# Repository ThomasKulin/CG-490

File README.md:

# CG-490
shooting stuff with electricity. yes

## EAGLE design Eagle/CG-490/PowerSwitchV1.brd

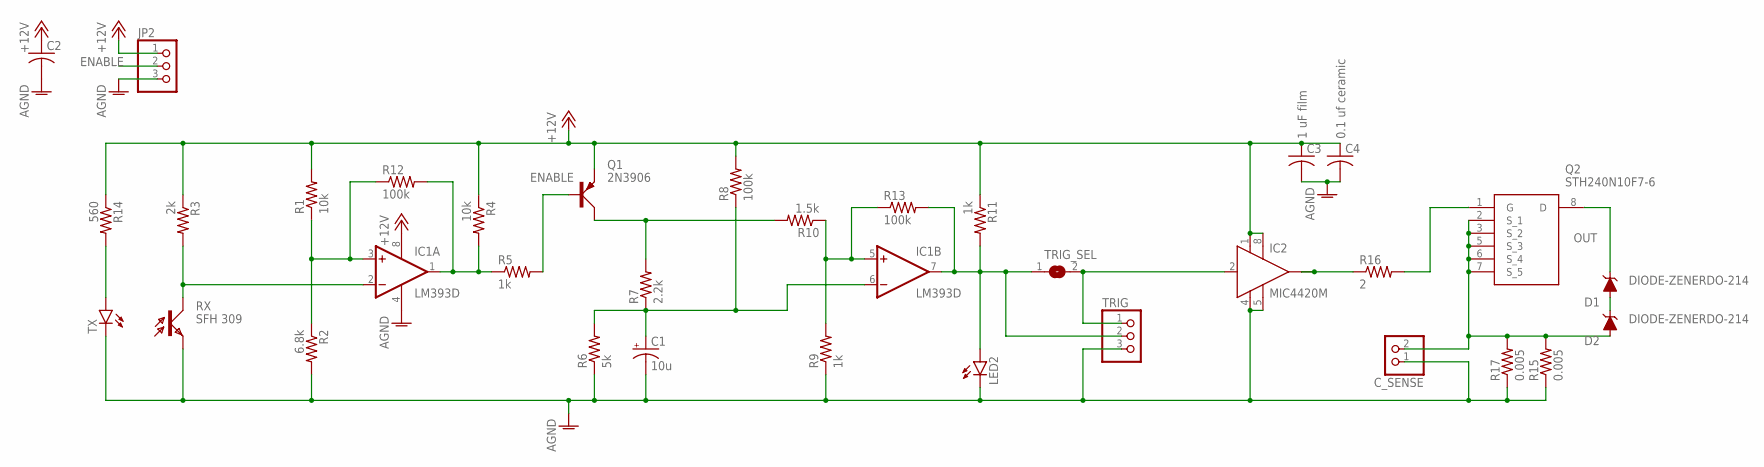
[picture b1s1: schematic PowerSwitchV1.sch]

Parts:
C1: 10u; TT2D6
C2: C-US050-050X075; C050-050X075
C3: 1 uF film; C050-045X075
C4: 0.1 uf ceramic; C025-030X050
C_SENSE: PINHD-1X2; 1X02
D1, D2: DIODE-ZENERDO-214; SMA-DIODE
IC1: LM393D; SO08
IC2: MIC4420M; SO-08
JP2: PINHD-1X3; 1X03
LED2: LEDCHIPLED_0603; CHIPLED_0603
Q1: 2N3906; TO92D
Q2: STH240N10F7-6; H2PAK-6_1
R1, R4: 10k; R0603
R2: 6.8k; R0603
R3: 2k; R0603
R5, R9, R11: 1k; R0603
R6: 5k; R0603
R7: 2.2k; R0603
R8, R12, R13: 100k; R0603
R10: 1.5k; R0603
R14: 560; R0603
R15, R17: 0.005; R1206
R16: 2; M0805
RX: SFH 309; BPX81
TRIG: PINHD-1X3; 1X03
TRIG_SEL: SJ
TX: LED3MM

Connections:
+12V: C2.1, C3.1, C4.1, IC1.8 (V+), IC2.1 (VS), IC2.8 (VS1), JP2.1, Q1.E, R1.2, R3.1, R4.1, R8.2, R11.1, R14.1
AGND: C1.-, C2.2, C3.2, C4.2, C_SENSE.1, IC1.4 (V-), IC2.4 (GND), IC2.5 (GND1), JP2.3, LED2.C, R2.2, R6.1, R9.1, R15.1, R17.1, RX.E, TRIG.3, TX.K (C)
ENABLE: JP2.2, Q1.B, R5.2
unnamed: IC1.2 (-IN), R3.2, RX.C
unnamed: IC2.2 (IN), TRIG.1, TRIG_SEL.2
unnamed: IC1.3 (+IN), R1.1, R2.1, R12.1
unnamed: IC2.6 (OUT), IC2.7 (OUT), R16.1
unnamed: IC1.1 (OUT), R4.2, R5.1, R12.2
unnamed: Q1.C, R7.2, R10.2
unnamed: C1.+, IC1.6 (-IN), R6.2, R7.1, R8.1
unnamed: R14.2, TX.A
unnamed: D1.A, D2.C
unnamed: IC1.5 (+IN), R9.2, R10.1, R13.1
unnamed: IC1.7 (OUT), LED2.A, R11.2, R13.2, TRIG.2, TRIG_SEL.1
unnamed: C_SENSE.2, D2.A, Q2.2 (S_1), Q2.3 (S_2), Q2.5 (S_3), Q2.6 (S_4), Q2.7 (S_5), R15.2, R17.2
unnamed: Q2.1 (G), R16.2
OUT: D1.C, Q2.8 (D)

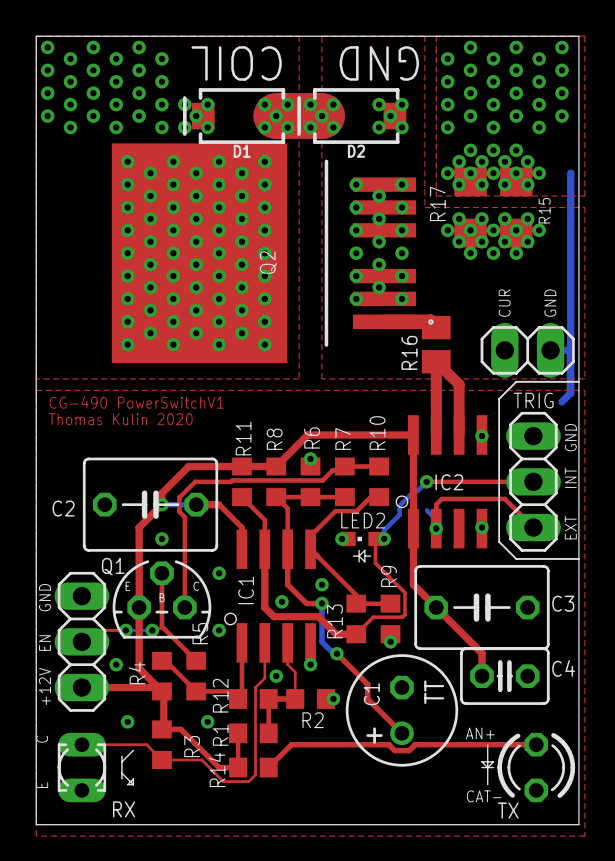
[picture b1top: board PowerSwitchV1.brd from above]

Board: 2 copper layers, 30.1 x 43.8 mm, 34 parts (1 on the bottom side), 17 nets.

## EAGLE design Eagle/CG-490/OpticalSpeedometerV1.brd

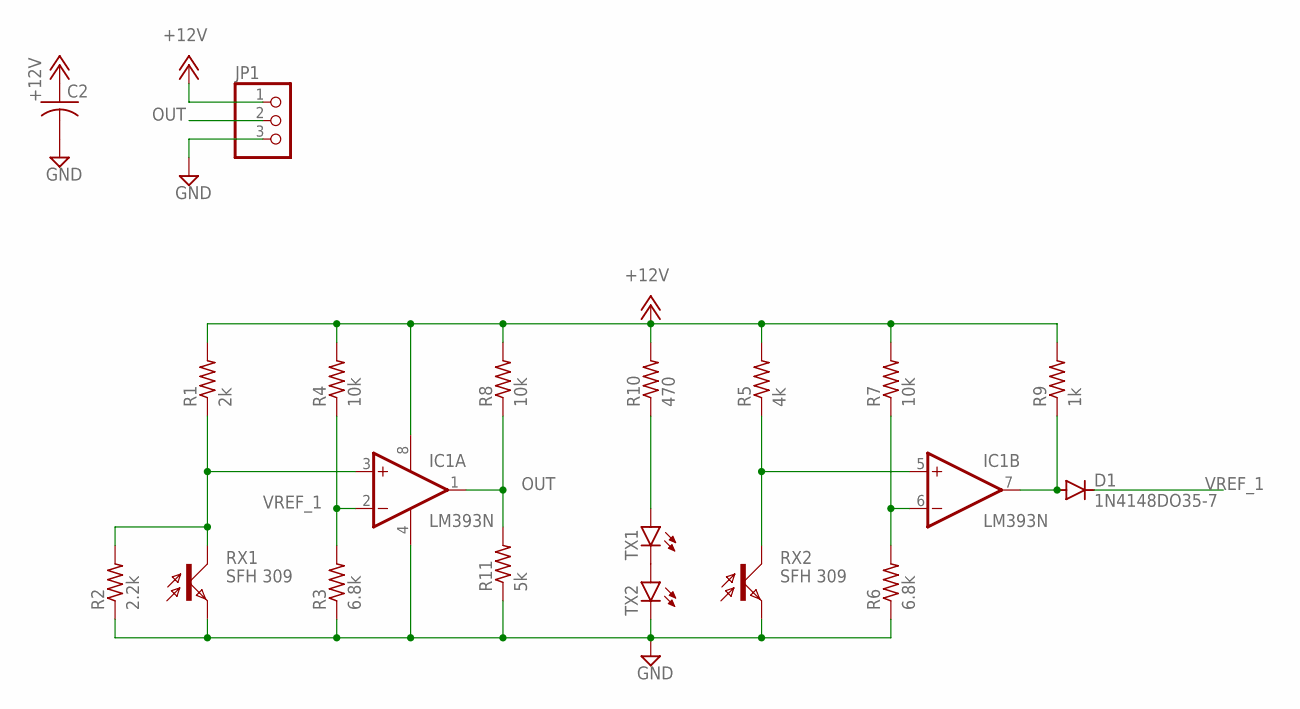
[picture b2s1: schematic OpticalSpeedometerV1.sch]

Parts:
C2: C-US050-050X075; C050-050X075
D1: 1N4148DO35-7; DO35-7
IC1: LM393N; DIL08
JP1: PINHD-1X3; 1X03
R1: 2k; 0204/5
R2: 2.2k; 0204/5
R3, R6: 6.8k; 0204/5
R4, R7, R8: 10k; 0204/5
R5: 4k; 0204/5
R9: 1k; 0204/5
R10: 470; 0204/5
R11: 5k; 0204/5
RX1, RX2: SFH 309; BPX81
TX1, TX2: LED3MM

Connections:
+12V: C2.1, IC1.8 (V+), JP1.1, R1.2, R4.2, R5.2, R7.2, R8.2, R9.2, R10.2
GND: C2.2, IC1.4 (V-), JP1.3, R2.1, R3.1, R6.1, R11.1, RX1.E, RX2.E, TX2.K (C)
unnamed: TX1.K (C), TX2.A
unnamed: IC1.3 (+IN), R1.1, R2.2, RX1.C
unnamed: R10.1, TX1.A
unnamed: IC1.5 (+IN), R5.1, RX2.C
unnamed: IC1.6 (-IN), R6.2, R7.1
unnamed: D1.A, IC1.7 (OUT), R9.1
OUT: IC1.1 (OUT), JP1.2, R8.1, R11.2
VREF_1: D1.C, IC1.2 (-IN), R3.2, R4.1

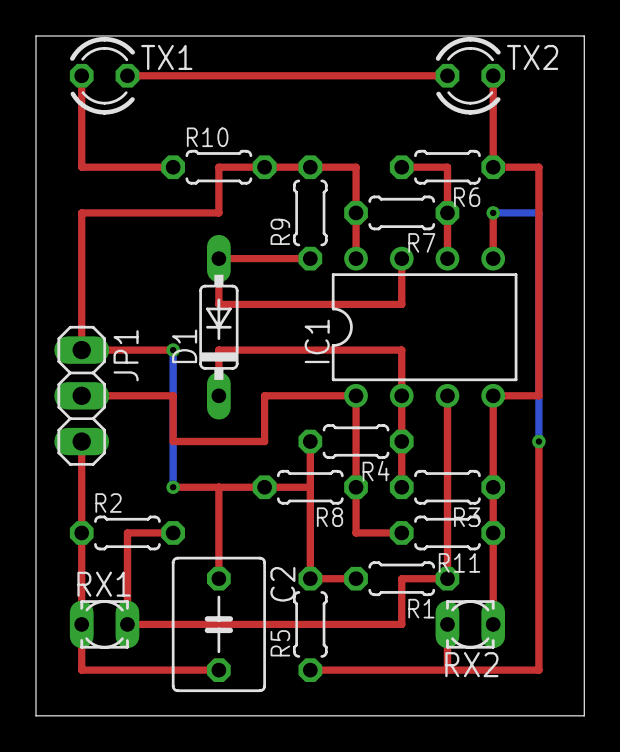
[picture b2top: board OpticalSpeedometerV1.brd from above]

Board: 2 copper layers, 30.5 x 37.8 mm, 19 parts (0 on the bottom side), 10 nets.

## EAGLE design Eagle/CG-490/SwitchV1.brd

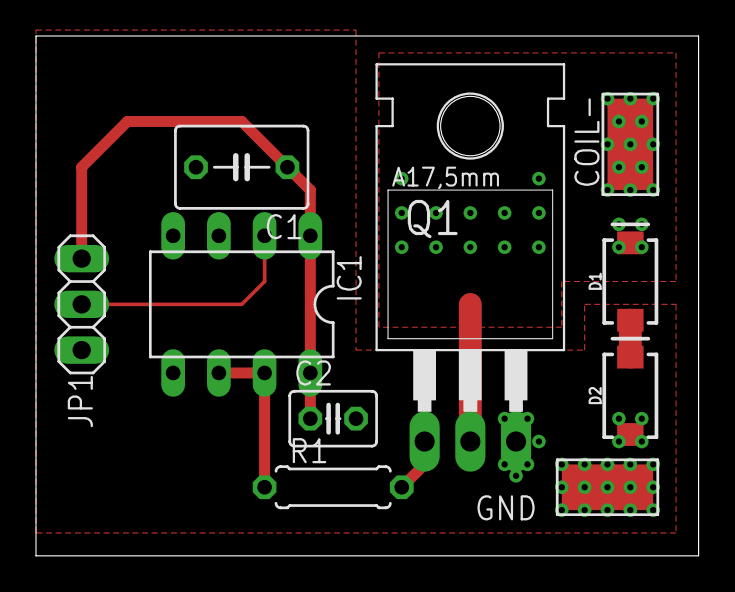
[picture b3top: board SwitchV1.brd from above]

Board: 2 copper layers, 36.8 x 28.9 mm, 10 parts (0 on the bottom side), 7 nets.

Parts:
C1: 1 uF film; C050-045X075
C2: 0.1 uf ceramic; C025-030X050
COIL-: WIREPADSMD5-2,5; 5-2,5
D1, D2: DIODE-ZENERDO-214; SMA-DIODE
GND: WIREPADSMD5-2,5; 5-2,5
IC1: MIC4420N; DIL08
JP1: 1X03
Q1: IRF540; TO220
R1: 1; 0207/7

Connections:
+18V: C1.1, C2.1, IC1.1, IC1.8, JP1.1
GND: C1.2, C2.2, D2.A, GND.1, IC1.4, IC1.5, JP1.3, Q1.3
unnamed: IC1.6, IC1.7, R1.1
unnamed: Q1.1, R1.2
unnamed: D1.A, D2.C
unnamed: IC1.2, JP1.2
OUT: COIL-.1, D1.C, Q1.2

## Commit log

2019-10-16 preliminary SPICE and FEMM simulations along with python automated tests in progress
2019-10-17 updated time sweep test, added thermal model to simulations
2019-10-18 atarted implementing a femm sim sweeping length, radius of projectile while maintaining a constant coil inductance
2019-10-21 dimensional sweep test functional. need to add better data capture
2019-10-22 ran some simulations to determine optimal projectile diameter for a 40uH coil, 12mm seems like the sweet spot. need to sweep length at that radius
2019-10-23 Added Inductance sweep test. Concludes that higher inductance is better but only a little. Width still has huge effects on the projectile..
2019-10-23 Started writing the simulation writeup report
2019-10-24 updated write-up
2019-10-25 updated doc, added new links
2019-10-29 started final cicuit model
2019-10-29 updated report
2019-10-29 added prototype switch schematic
2019-10-30 added prototype layout and added to report
2019-10-30 started FEMM sim write-up, finished switch sim write-up
2019-10-31 added fixed resistance mode for FEMM sims
2019-11-01 fixed fixedresistance mode. captured length dimension sweep with constant resistance. wrote some stuff. hi thomas
2019-11-01 added some stuff but i dont remember what
2019-11-05 added 2d plots for dimension sweep
2019-11-12 added LT Spice simulation integration into python scripts to facilitate more accurate simulation at higher inductances
2019-11-13 started updated timesweep test
2019-11-14 completed integration of current waveform in time based simulation. Next step is to make it multi stage
2019-11-14 got some nice data
2019-11-14 completed simultion of first stage, started simulation of subsequent stages, updated report
2019-11-20 not much
2019-11-21 designed optical trigger with pulse limiting mechanism, ran LT simulations
2019-11-22 updated optical switch schematic. needs better biasing on comparator 2 to ensure noise proof performance. also editing report.
2019-11-24 Added time based external iron test and object
2019-11-25 worked on report
2019-11-25 did some external iron testing for stage 1. Not feasible
2019-11-26 first commie
2020-01-31 ran simulation of real world stage 1 design, created optical assembly CAD file
2020-02-10 updated report with opt triggering circuit performance and finalized magnetic sim for first stage
2020-02-13 fuck, i just shorted the LIPO through a bunch of shit....
2020-03-05 layout for optical trigger and complete circuit underway
2020-03-05 updated document with test results
2020-03-05 updated board layouts
2020-03-06 updated components in 3d model of PCB
2020-03-10 finalized schematic/pcb, updated report
2020-03-12 updated board layout
2020-03-19 idk, just syncing
2020-03-22 made optical speed sensor sim, circuit and perfboard layout
2020-09-17 updated report and made minor changes with the boys
2021-10-10 sync

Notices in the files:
parts and their libraries:
sparkfun-discretesemi: Licensing: Creative Commons ShareAlike 4.0 International - https://creativecommons.org/licenses/by-sa/4.0
